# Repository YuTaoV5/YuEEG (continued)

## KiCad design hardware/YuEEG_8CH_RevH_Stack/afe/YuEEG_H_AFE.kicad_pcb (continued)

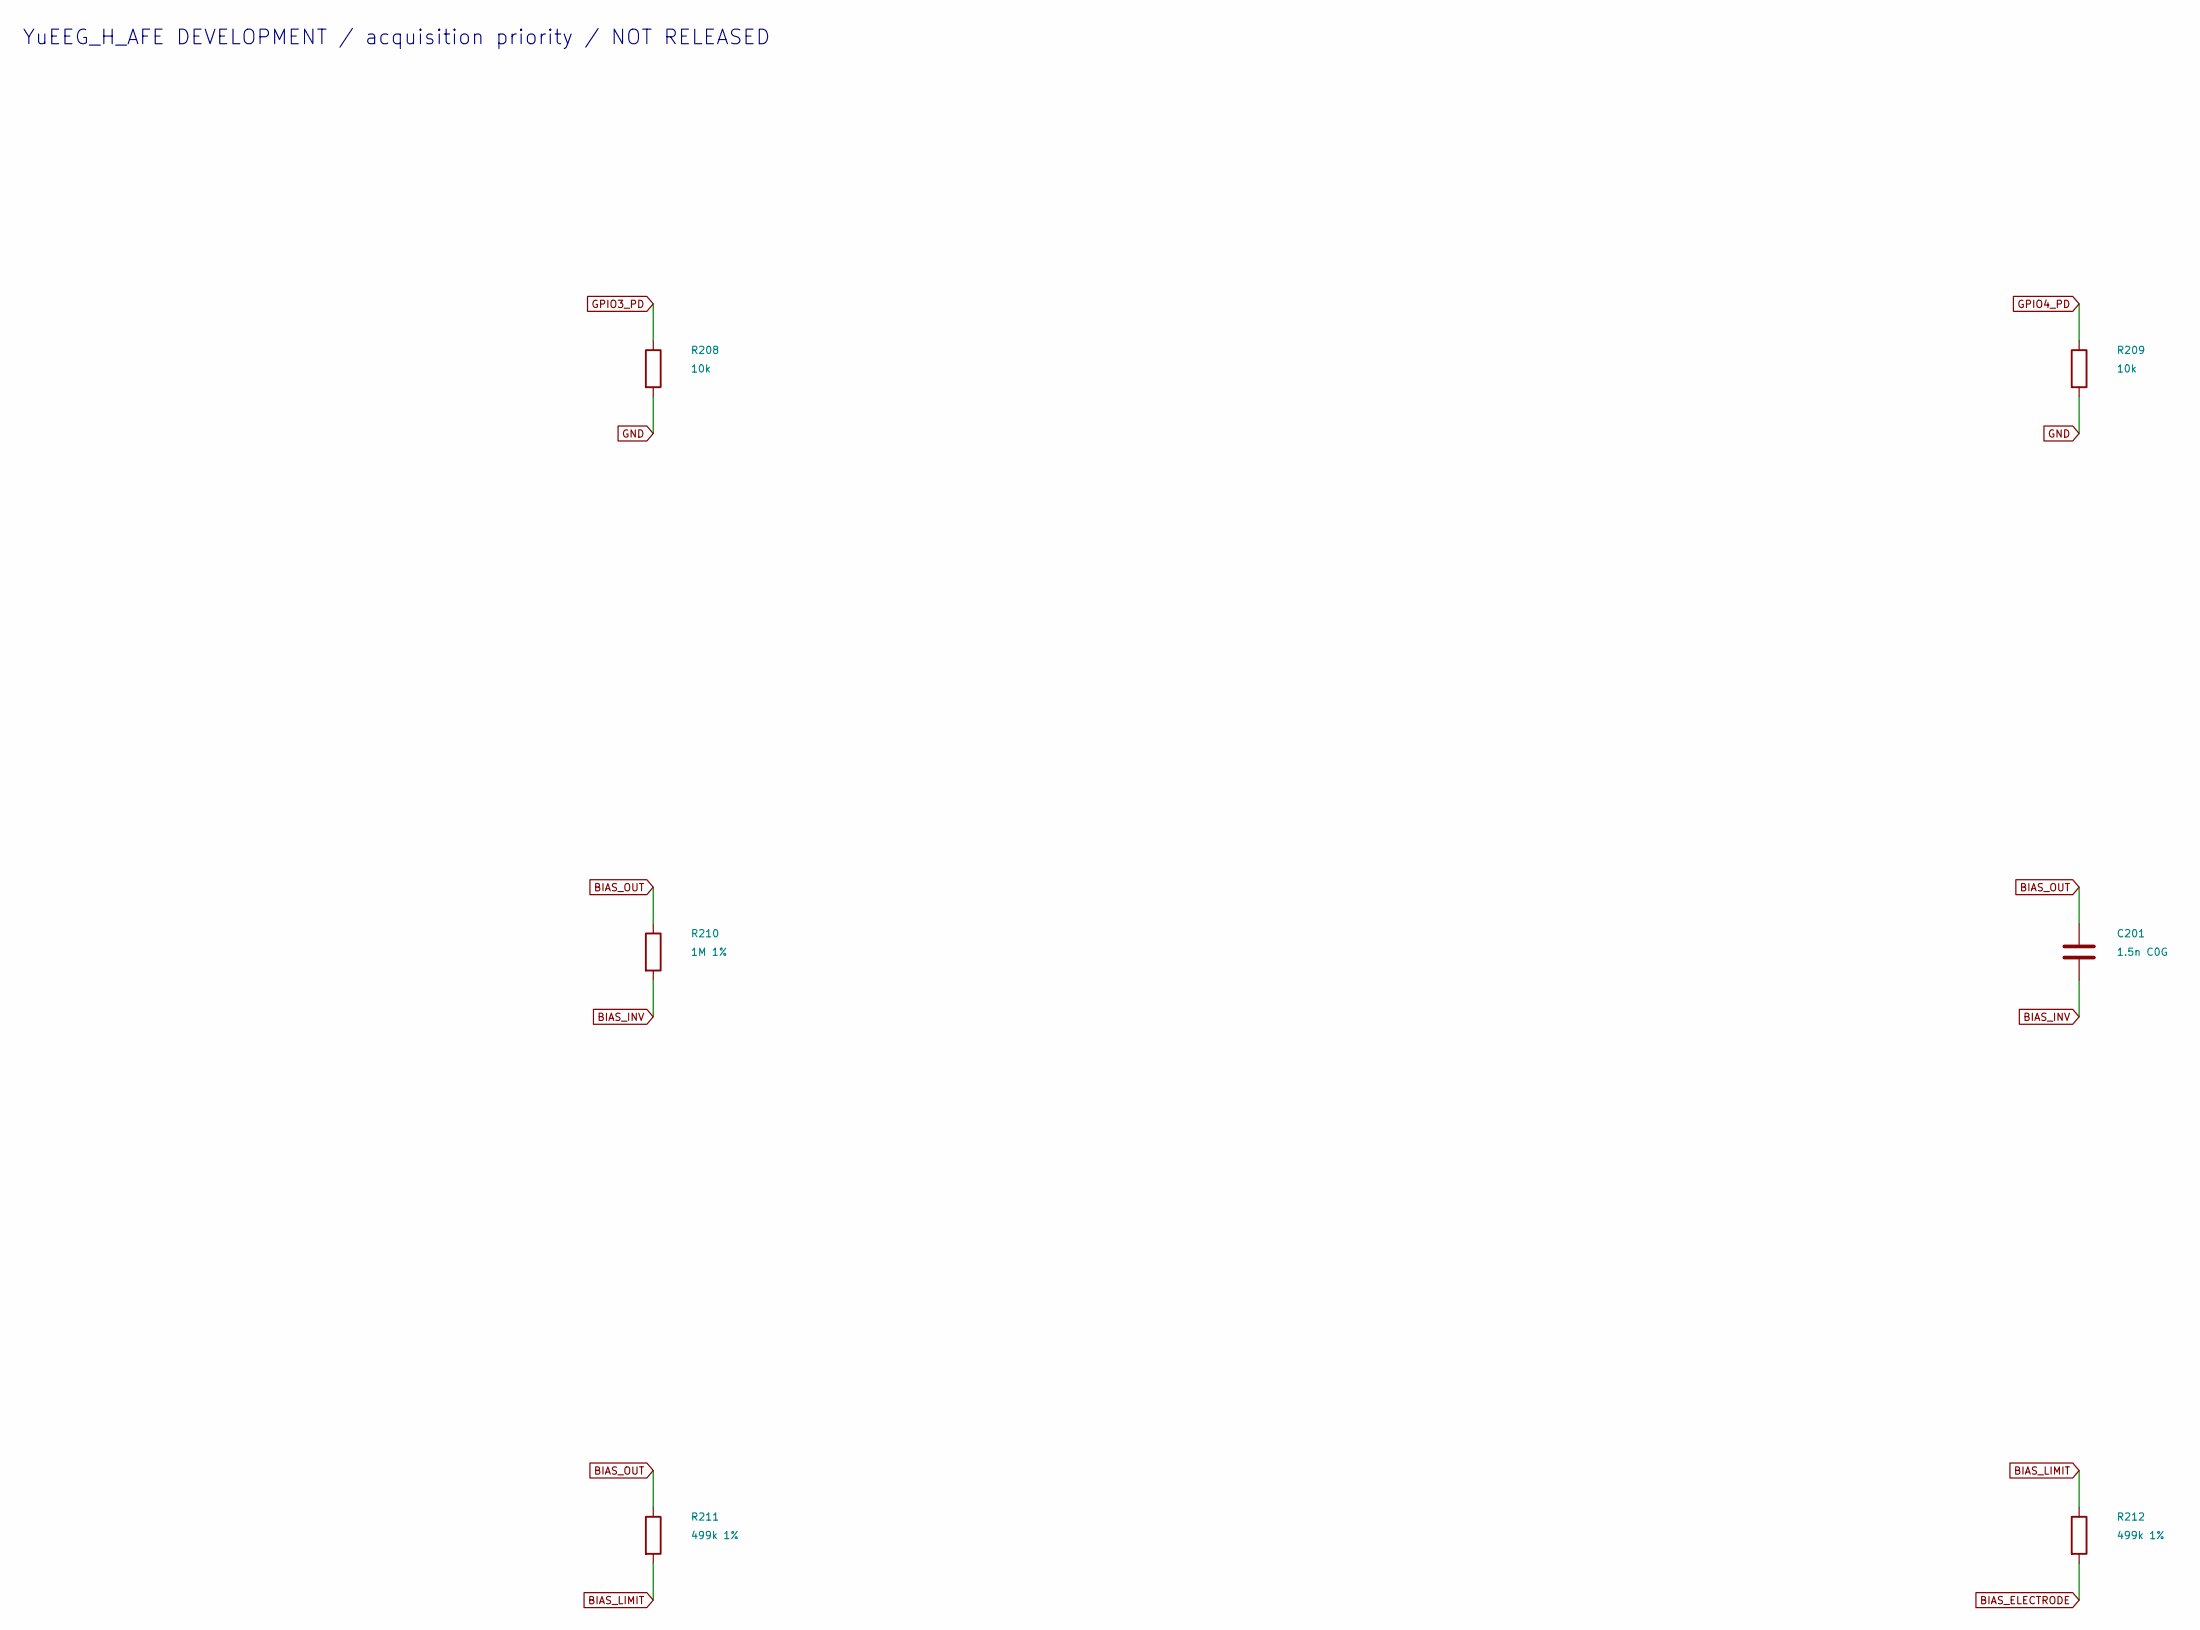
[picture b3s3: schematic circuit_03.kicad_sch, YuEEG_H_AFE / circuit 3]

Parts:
C201: 1.5n C0G; C_0402_1005Metric
R208, R209: 10k; R_0402_1005Metric
R210: 1M 1%; R_0402_1005Metric
R211, R212: 499k 1%; R_0402_1005Metric

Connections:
BIAS_ELECTRODE: R212.2; also elsewhere on the board
BIAS_INV: C201.2, R210.2; also elsewhere on the board
BIAS_LIMIT: R211.2, R212.1; also elsewhere on the board
BIAS_OUT: C201.1, R210.1, R211.1; also elsewhere on the board
GND: R208.2, R209.2; also elsewhere on the board
GPIO3_PD: R208.1; also elsewhere on the board
GPIO4_PD: R209.1; also elsewhere on the board

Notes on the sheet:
YuEEG_H_AFE DEVELOPMENT / acquisition priority / NOT RELEASED

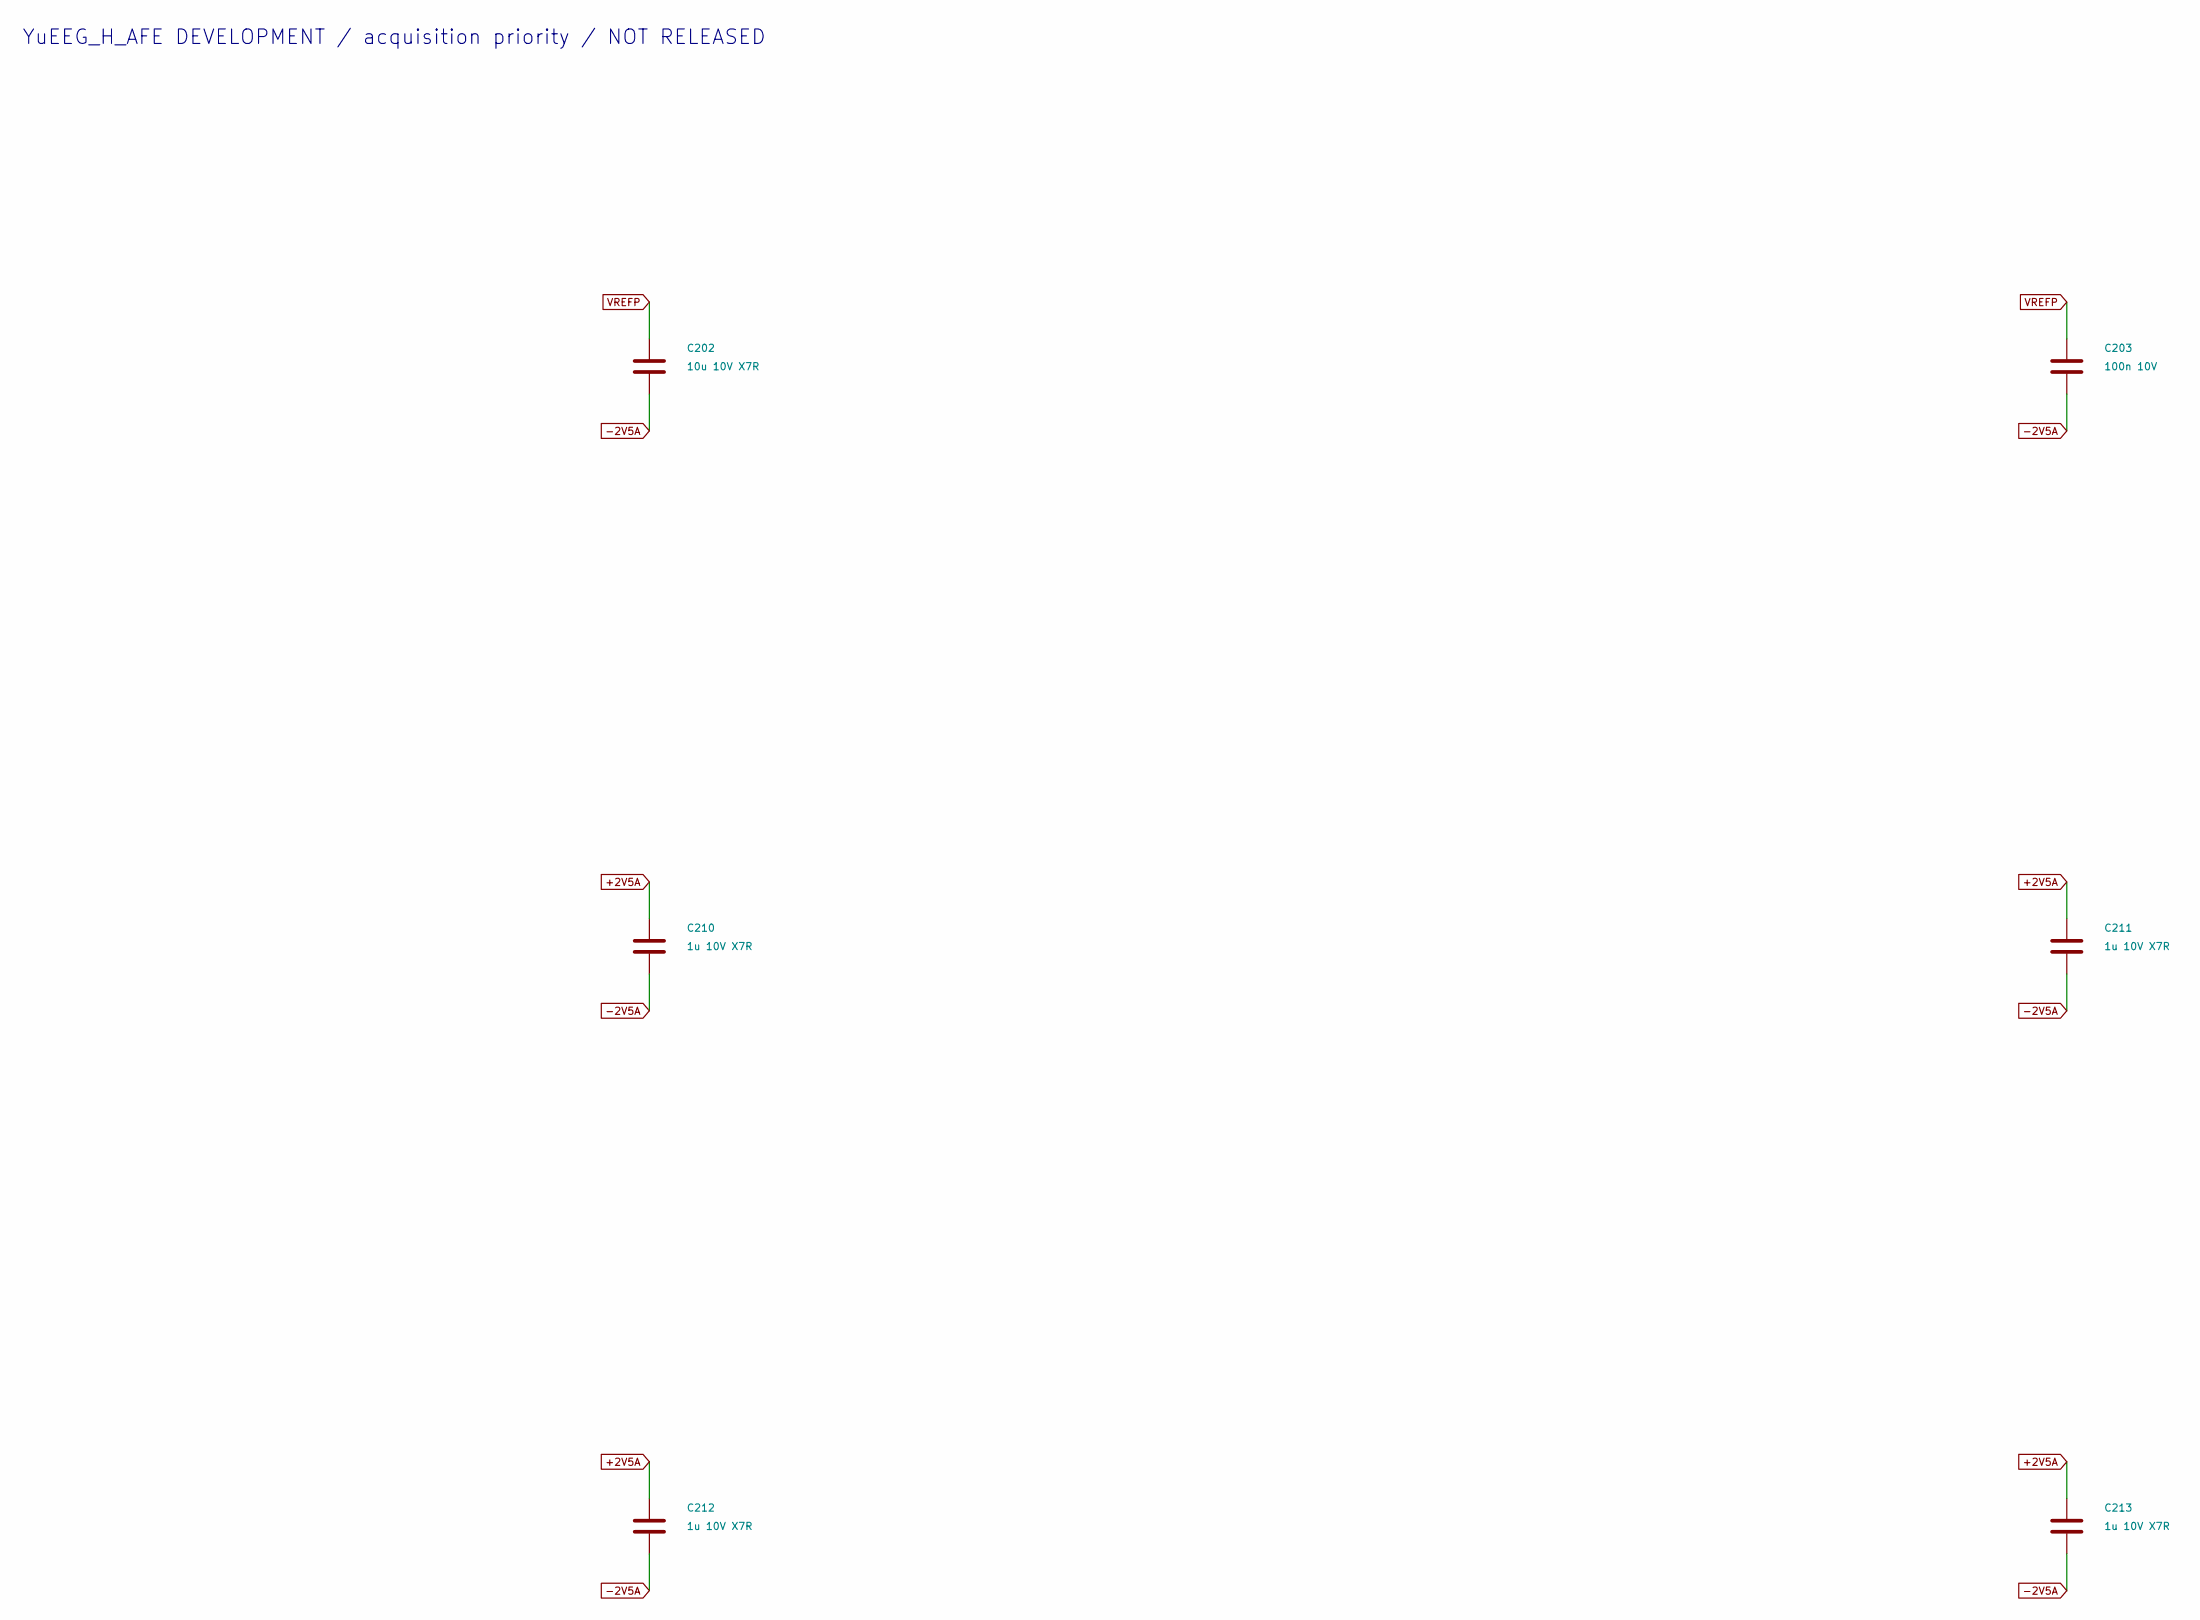
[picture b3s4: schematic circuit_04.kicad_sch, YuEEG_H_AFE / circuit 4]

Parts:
C202: 10u 10V X7R; C_0805_2012Metric
C203: 100n 10V; C_0402_1005Metric
C210, C211, C212, C213: 1u 10V X7R; C_0603_1608Metric

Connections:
+2V5A: C210.1, C211.1, C212.1, C213.1; also elsewhere on the board
-2V5A: C202.2, C203.2, C210.2, C211.2, C212.2, C213.2; also elsewhere on the board
VREFP: C202.1, C203.1; also elsewhere on the board

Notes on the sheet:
YuEEG_H_AFE DEVELOPMENT / acquisition priority / NOT RELEASED

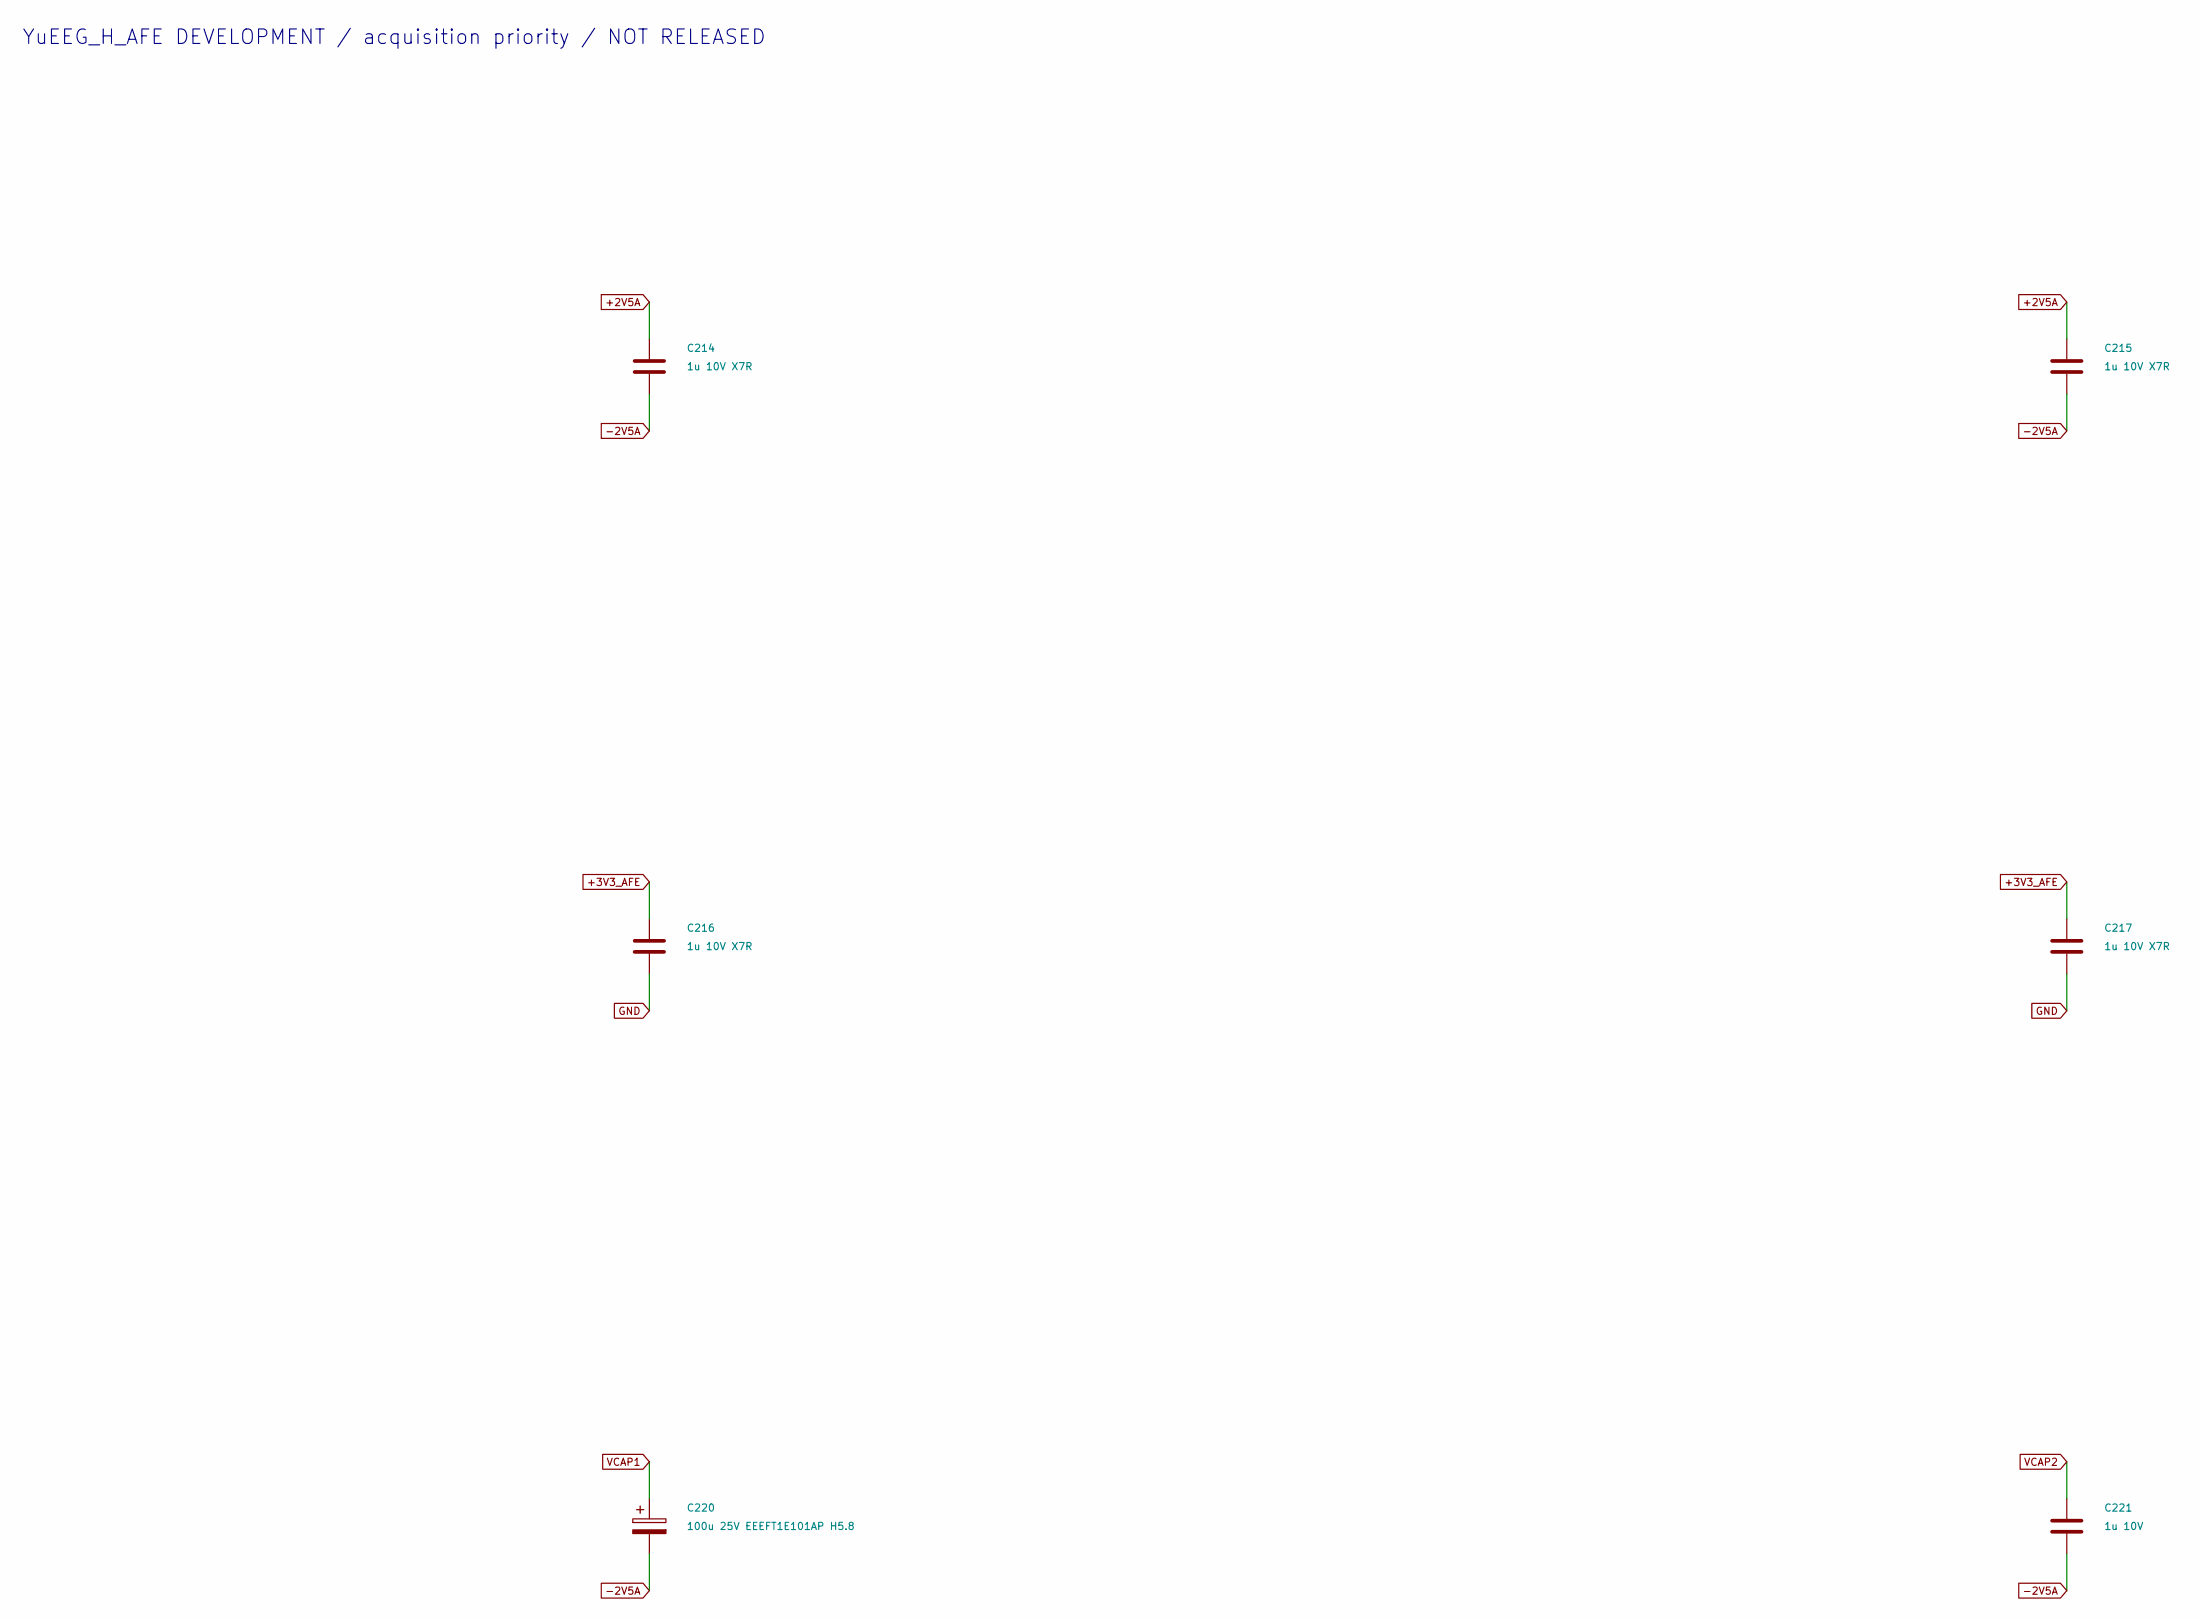
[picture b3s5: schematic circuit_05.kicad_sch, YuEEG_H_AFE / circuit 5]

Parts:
C214, C215, C216, C217: 1u 10V X7R; C_0603_1608Metric
C220: 100u 25V EEEFT1E101AP H5.8; CP_Elec_6.3x5.8
C221: 1u 10V; C_0603_1608Metric

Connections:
+2V5A: C214.1, C215.1; also elsewhere on the board
+3V3_AFE: C216.1, C217.1; also elsewhere on the board
-2V5A: C214.2, C215.2, C220.2, C221.2; also elsewhere on the board
GND: C216.2, C217.2; also elsewhere on the board
VCAP1: C220.1; also elsewhere on the board
VCAP2: C221.1; also elsewhere on the board

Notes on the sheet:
YuEEG_H_AFE DEVELOPMENT / acquisition priority / NOT RELEASED

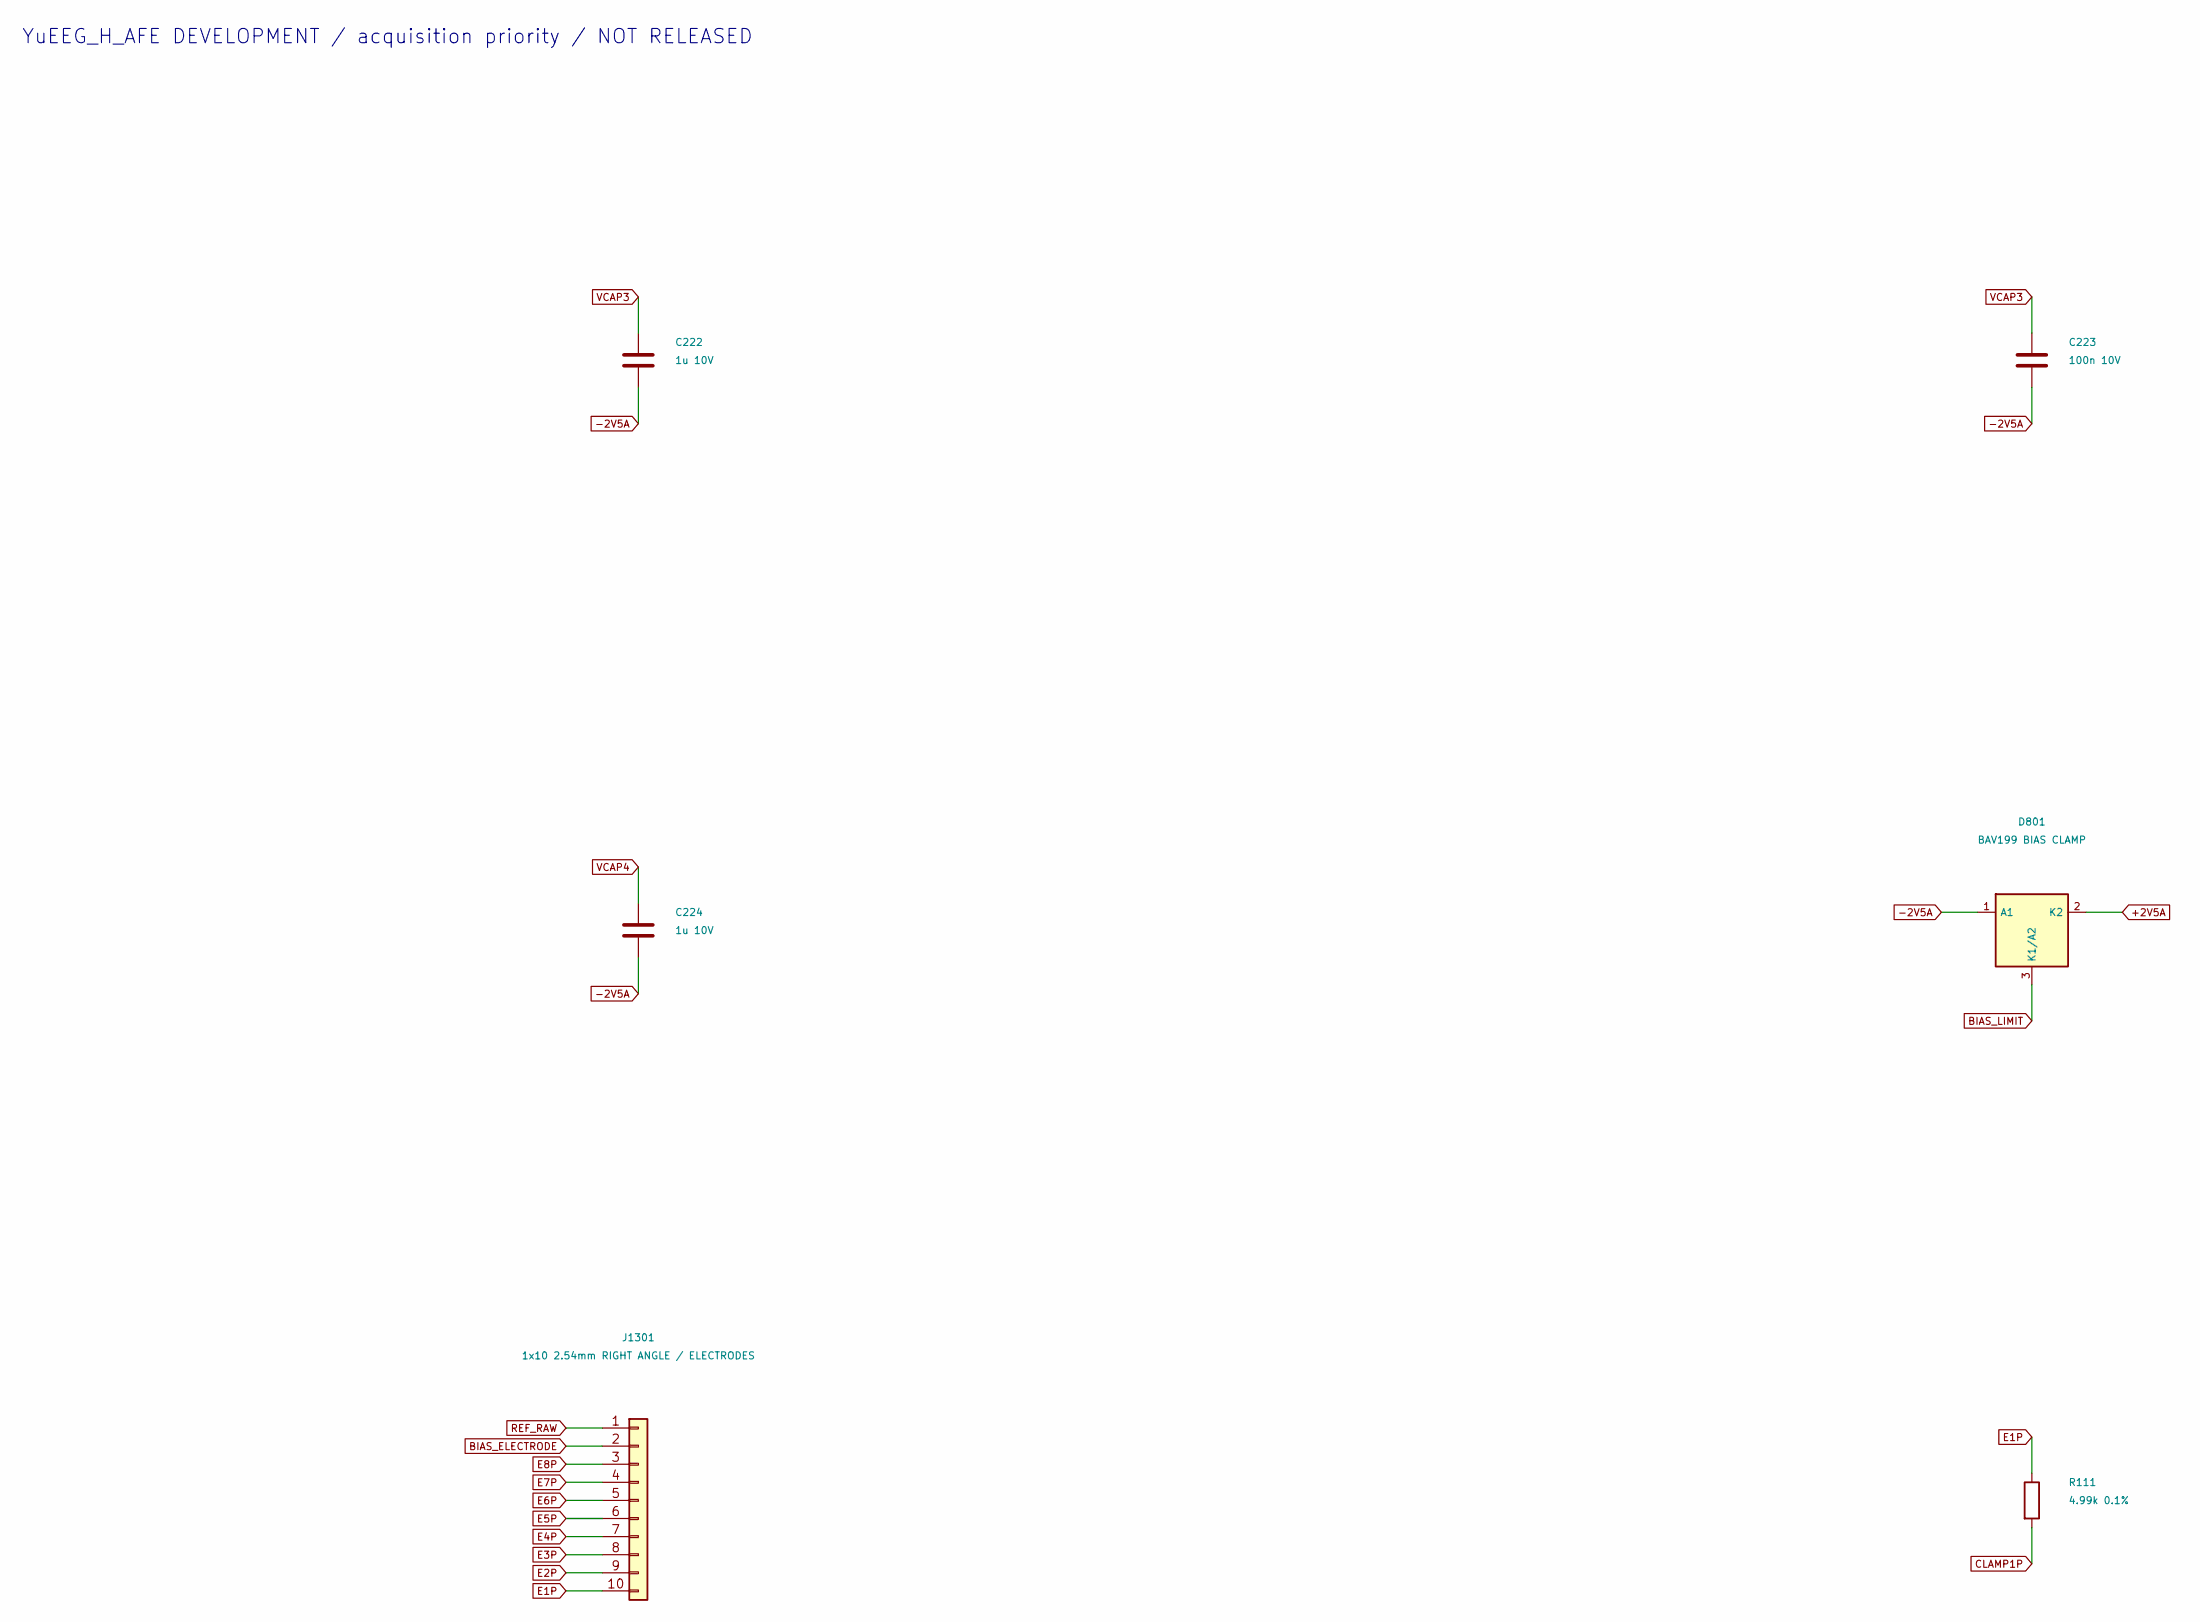
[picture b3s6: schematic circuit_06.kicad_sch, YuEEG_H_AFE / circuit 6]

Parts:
C222, C224: 1u 10V; C_0603_1608Metric
C223: 100n 10V; C_0402_1005Metric
D801: BAV199 BIAS CLAMP; SOT-23
J1301: 1x10 2.54mm RIGHT ANGLE / ELECTRODES; Electrode_1x10_Horizontal_ReverseLogical
R111: 4.99k 0.1%; R_0402_1005Metric

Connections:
+2V5A: D801.2 (K2); also elsewhere on the board
-2V5A: C222.2, C223.2, C224.2, D801.1 (A1); also elsewhere on the board
BIAS_ELECTRODE: J1301.2; also elsewhere on the board
BIAS_LIMIT: D801.3 (K1/A2); also elsewhere on the board
CLAMP1P: R111.2; also elsewhere on the board
E1P: J1301.10, R111.1
E2P: J1301.9; also elsewhere on the board
E3P: J1301.8; also elsewhere on the board
E4P: J1301.7; also elsewhere on the board
E5P: J1301.6; also elsewhere on the board
E6P: J1301.5; also elsewhere on the board
E7P: J1301.4; also elsewhere on the board
E8P: J1301.3; also elsewhere on the board
REF_RAW: J1301.1; also elsewhere on the board
VCAP3: C222.1, C223.1; also elsewhere on the board
VCAP4: C224.1; also elsewhere on the board

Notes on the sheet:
YuEEG_H_AFE DEVELOPMENT / acquisition priority / NOT RELEASED

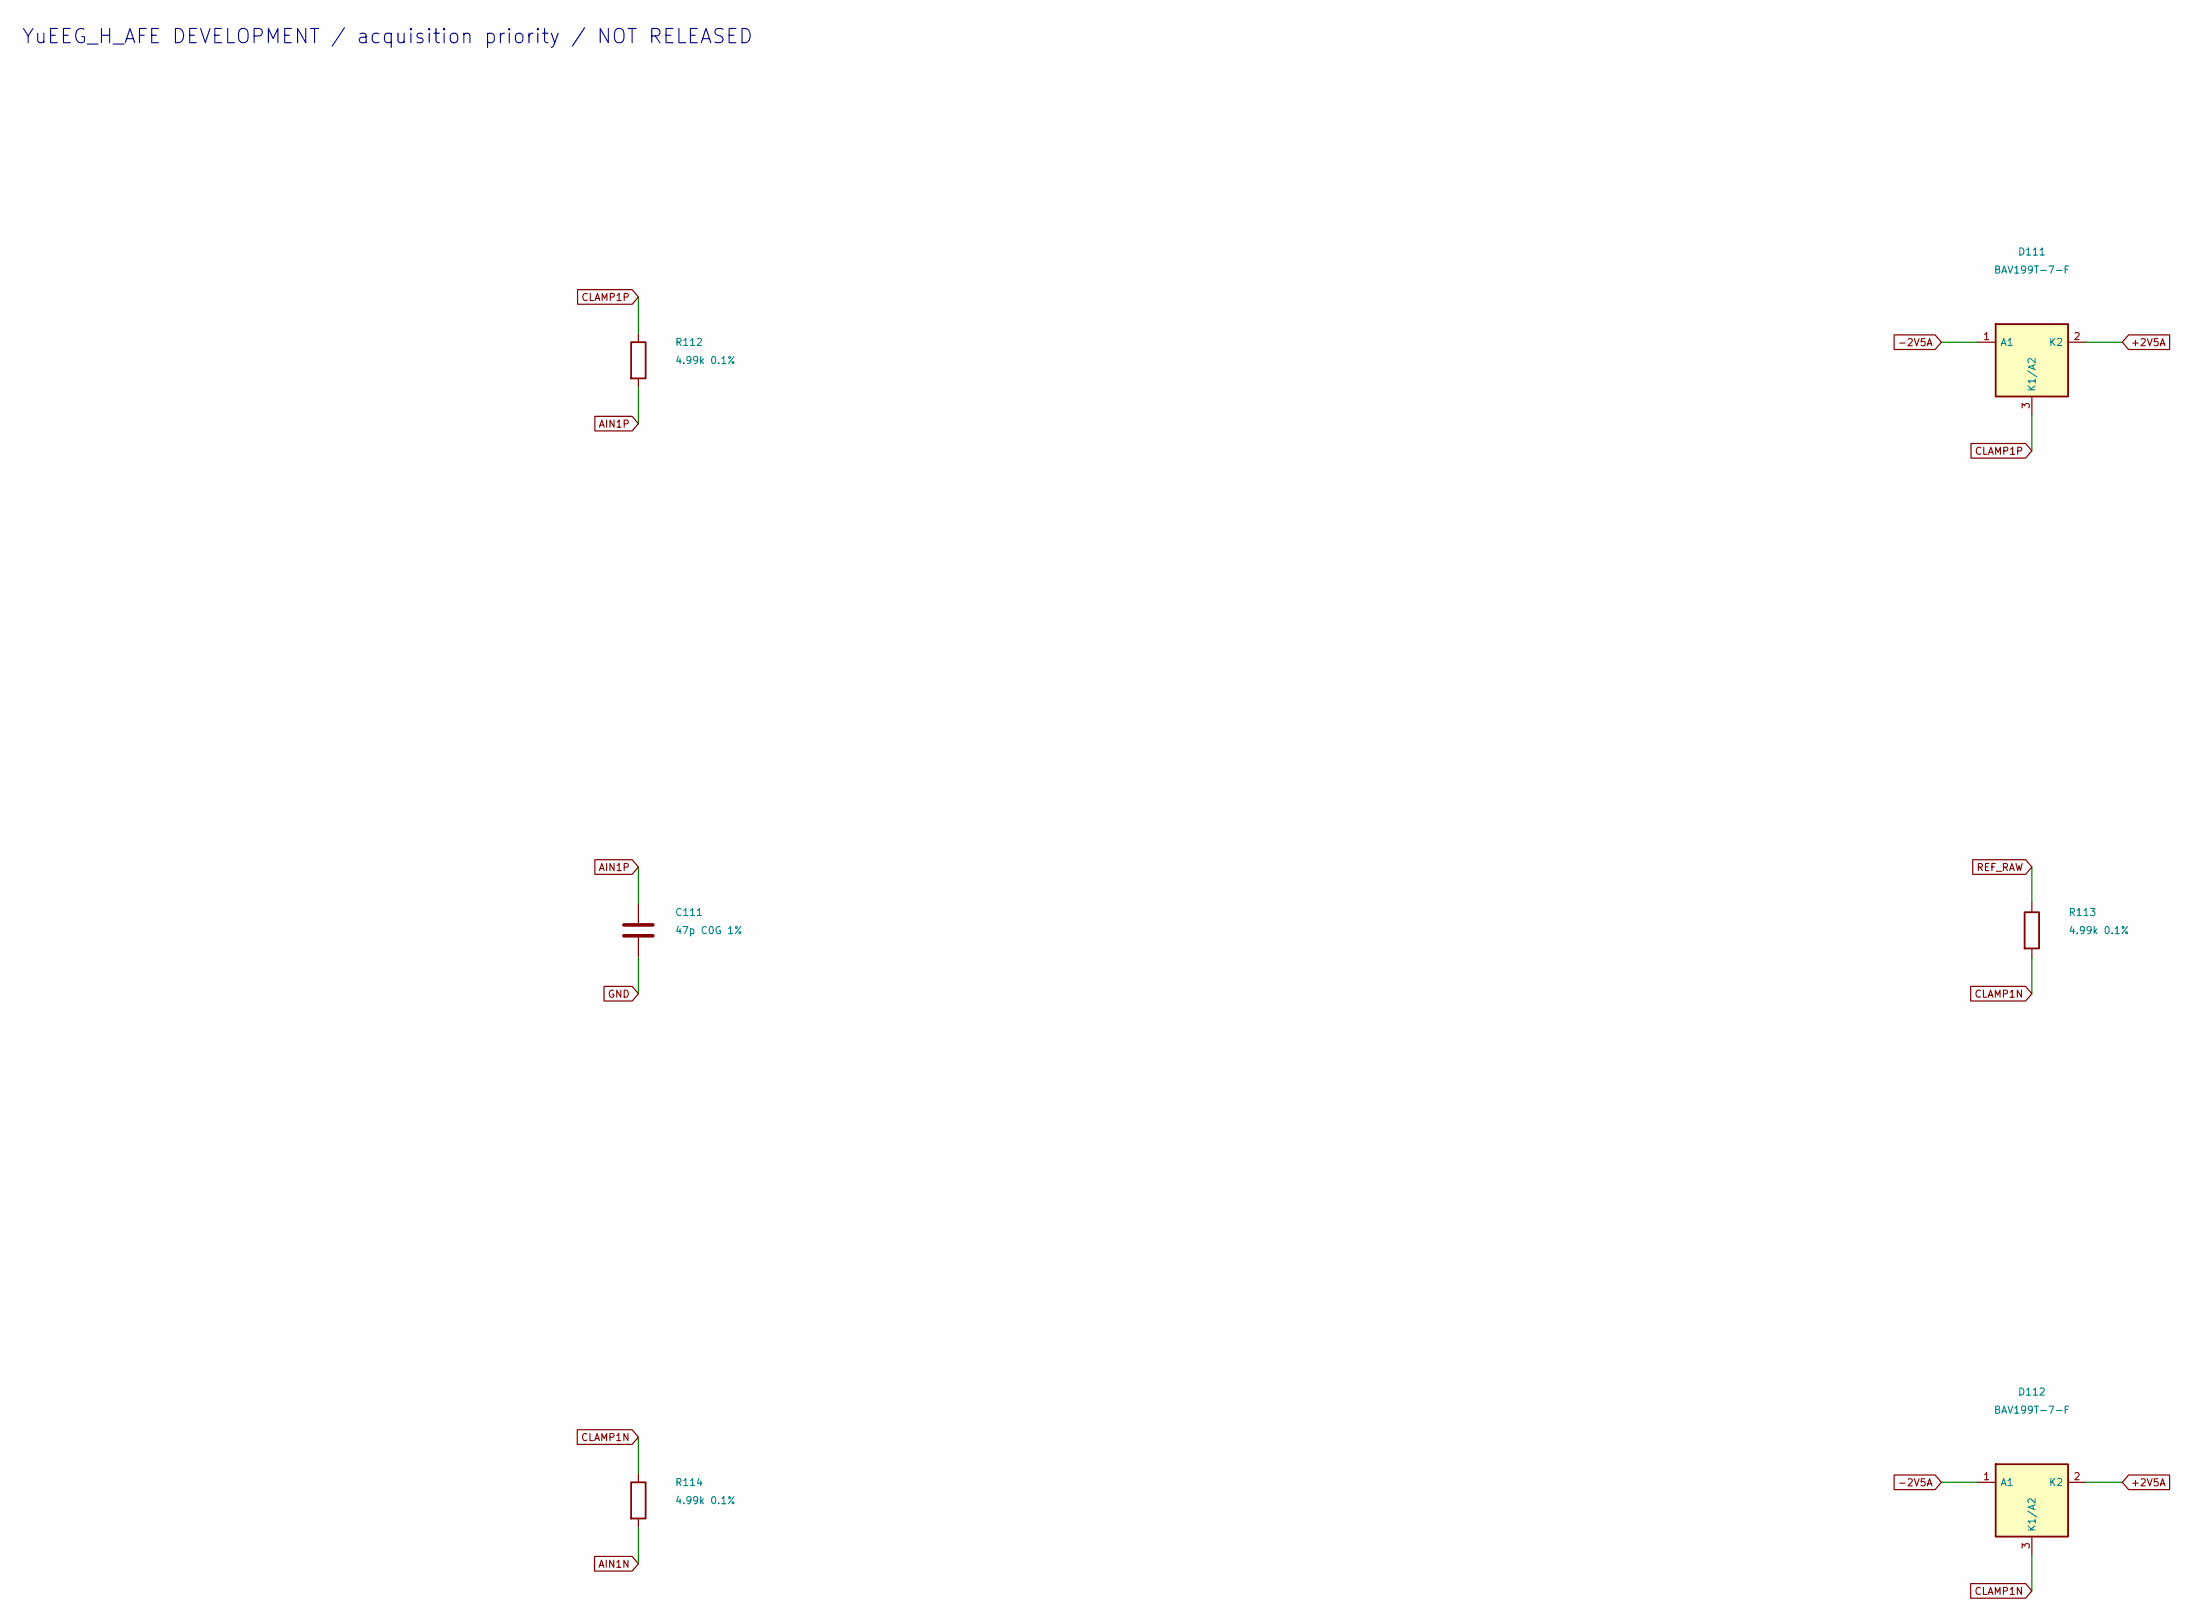
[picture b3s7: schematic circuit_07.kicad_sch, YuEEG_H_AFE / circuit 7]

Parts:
C111: 47p C0G 1%; C_0402_1005Metric
D111, D112: BAV199T-7-F; SOT-523
R112, R113, R114: 4.99k 0.1%; R_0402_1005Metric

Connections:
+2V5A: D111.2 (K2), D112.2 (K2); also elsewhere on the board
-2V5A: D111.1 (A1), D112.1 (A1); also elsewhere on the board
AIN1N: R114.2; also elsewhere on the board
AIN1P: C111.1, R112.2; also elsewhere on the board
CLAMP1N: D112.3 (K1/A2), R113.2, R114.1
CLAMP1P: D111.3 (K1/A2), R112.1; also elsewhere on the board
GND: C111.2; also elsewhere on the board
REF_RAW: R113.1; also elsewhere on the board

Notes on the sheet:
YuEEG_H_AFE DEVELOPMENT / acquisition priority / NOT RELEASED
